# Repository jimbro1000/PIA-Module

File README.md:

# HD6309SBC PIA Prototype Module Board

This is an expansion board for the HD6309 
single board computer I designed (see 
https://github.com/jimbro1000/HD6309sbc).

The board uses the highly adaptable
MC6821 as the basis of the design but it
is advised to use the WDC65C21N as a 
substitute to guarantee handling of the
3MHz clock speed used by default.

Dropping the clock speed on the main
compute board will allow the use of
lower rated PIAs

By default the MC6821 is rated at only
1MHz.  
The A rated chip (68A21) is safe to 1.5MHz.  
The B rated chip (68B21) is safe to 2MHz.

Compatible variants are similarly rated
and also top out at 2MHz.

The board includes an 8x32 prototype area
while PL1 exposes all 16 data lanes
available to the PIA. PL2 exposes the
4 PIA control lines (CA0,CA1,CB0,CB1) and
various useful signals from the main
board along with +5V and GND.

The available signal lines are CPU clock
and switched control bits Q1-Q7

## Addressing

By default the PIA is addressable at $xx00 
through to $xx03. Optionally the addressing
can be modified to sit at $xx04 (to $xx07).

The value of xx is determined and managed by
the "mapped memory" signal line, this is
expected to be set to $FF00, so the default
PIA address is $FF00.

Each PIA block offers four registers:

* $FF00 = PIA Data Register A (PA0-PA7) or
Data Direction Register A
* $FF01 = PIA Control Register A
* $FF02 = PIA Data Register B (PB0-PB7) or
Data Direction Register B
* $FF03 = PIA Control Register B

## Example Usage - Keyboard Input

The PIA can be programmed to scan an 8x8
keyboard matrix, using PA0-PA7 for the
vertical and PB0-PB7 for the horizontal

The scan needs to be triggered on a timed
basis to scan and expose the captured data
on the main data bus

The control registers for both sides of
the PIA need to be set for input and this
needs a sequence of writes:

1. bit 2 of control register A must be
set low
2. input bits of data register A must
be set low
3. bit 2 of control register A must be
set high
4. bit 2 of control register B must be
set low
5. output bits of data register B must
be set high
6. bit 2 of control register B must be
set high

This leaves the relevant bits of data
registers A and B in input mode and 
the data registers exposed to the
address bus. Not all of the bits need
to be used and this will be determined
by the keyboard matrix. For example
the CoCo and Dragon keyboard matrices
use a 7x8 matrix (this *is* a 6809 based
computer).

In effect the single bits of register B
are set high in sequence, and at each
step register A is scanned to see which
keys are pressed for the given row or
column (depending on which way the 
matrix is oriented)

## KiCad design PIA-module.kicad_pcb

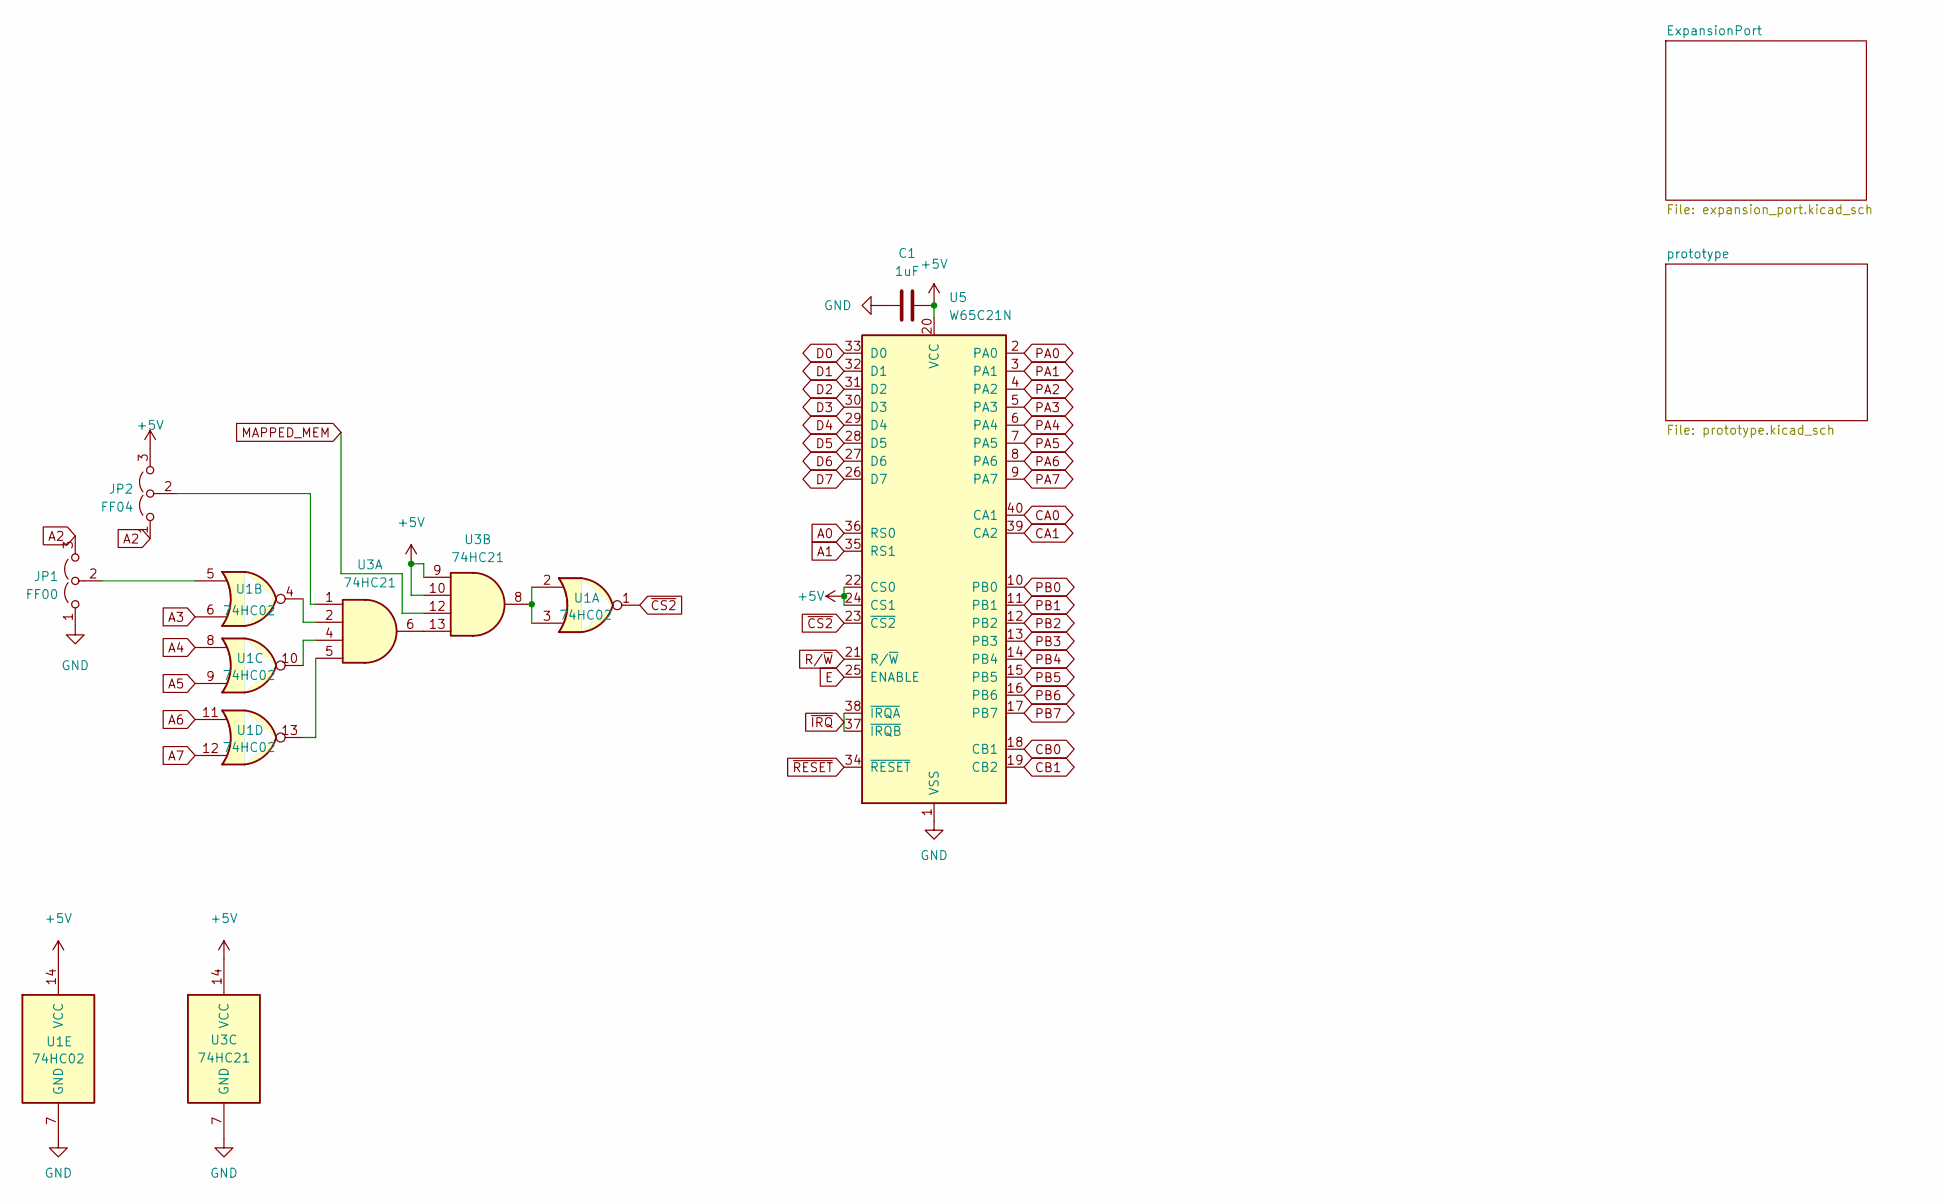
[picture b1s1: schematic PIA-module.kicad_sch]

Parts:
C1: 1uF; C_0805_2012Metric
JP1: FF00; PinHeader_1x03_P2.54mm_Vertical
JP2: FF04; PinHeader_1x03_P2.54mm_Vertical
U1: 74HC02; SO-14_3.9x8.65mm_P1.27mm
U3: 74HC21; SO-14_3.9x8.65mm_P1.27mm
U5: W65C21N; DIP-40_W15.24mm

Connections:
+5V: C1.1, JP2.3 (B), U1.14 (VCC), U3.9, U3.10, U3.14 (VCC), U5.20 (VCC), U5.22 (CS0), U5.24 (CS1); also elsewhere on the board
A0: U5.36 (RS0); also elsewhere on the board
A1: U5.35 (RS1); also elsewhere on the board
A2: JP1.3 (B), JP2.1 (A); also elsewhere on the board
A3: U1.6; also elsewhere on the board
A4: U1.8; also elsewhere on the board
A5: U1.9; also elsewhere on the board
A6: U1.11; also elsewhere on the board
A7: U1.12; also elsewhere on the board
CA0: U5.40 (CA1); also elsewhere on the board
CA1: U5.39 (CA2); also elsewhere on the board
CB0: U5.18 (CB1); also elsewhere on the board
CB1: U5.19 (CB2); also elsewhere on the board
D0: U5.33 (D0); also elsewhere on the board
D1: U5.32 (D1); also elsewhere on the board
D2: U5.31 (D2); also elsewhere on the board
D3: U5.30 (D3); also elsewhere on the board
D4: U5.29 (D4); also elsewhere on the board
D5: U5.28 (D5); also elsewhere on the board
D6: U5.27 (D6); also elsewhere on the board
D7: U5.26 (D7); also elsewhere on the board
E: U5.25 (ENABLE); also elsewhere on the board
GND: C1.2, JP1.1 (A), U1.7 (GND), U3.7 (GND), U5.1 (VSS); also elsewhere on the board
MAPPED_MEM: U3.12; also elsewhere on the board
unnamed: JP1.2 (C), U1.5
unnamed: JP2.2 (C), U3.1
unnamed: U1.2, U1.3, U3.8
unnamed: U1.4, U3.2
unnamed: U1.10, U3.4
unnamed: U1.13, U3.5
unnamed: U3.6, U3.13
PA0: U5.2 (PA0); also elsewhere on the board
PA1: U5.3 (PA1); also elsewhere on the board
PA2: U5.4 (PA2); also elsewhere on the board
PA3: U5.5 (PA3); also elsewhere on the board
PA4: U5.6 (PA4); also elsewhere on the board
PA5: U5.7 (PA5); also elsewhere on the board
PA6: U5.8 (PA6); also elsewhere on the board
PA7: U5.9 (PA7); also elsewhere on the board
PB0: U5.10 (PB0); also elsewhere on the board
PB1: U5.11 (PB1); also elsewhere on the board
PB2: U5.12 (PB2); also elsewhere on the board
PB3: U5.13 (PB3); also elsewhere on the board
PB4: U5.14 (PB4); also elsewhere on the board
PB5: U5.15 (PB5); also elsewhere on the board
PB6: U5.16 (PB6); also elsewhere on the board
PB7: U5.17 (PB7); also elsewhere on the board
R/~W: U5.21 (R/~W); also elsewhere on the board
~CS2: U1.1, U5.23 (~CS2)
~IRQ: U5.37 (~IRQB), U5.38 (~IRQA); also elsewhere on the board
~RESET: U5.34 (~RESET); also elsewhere on the board

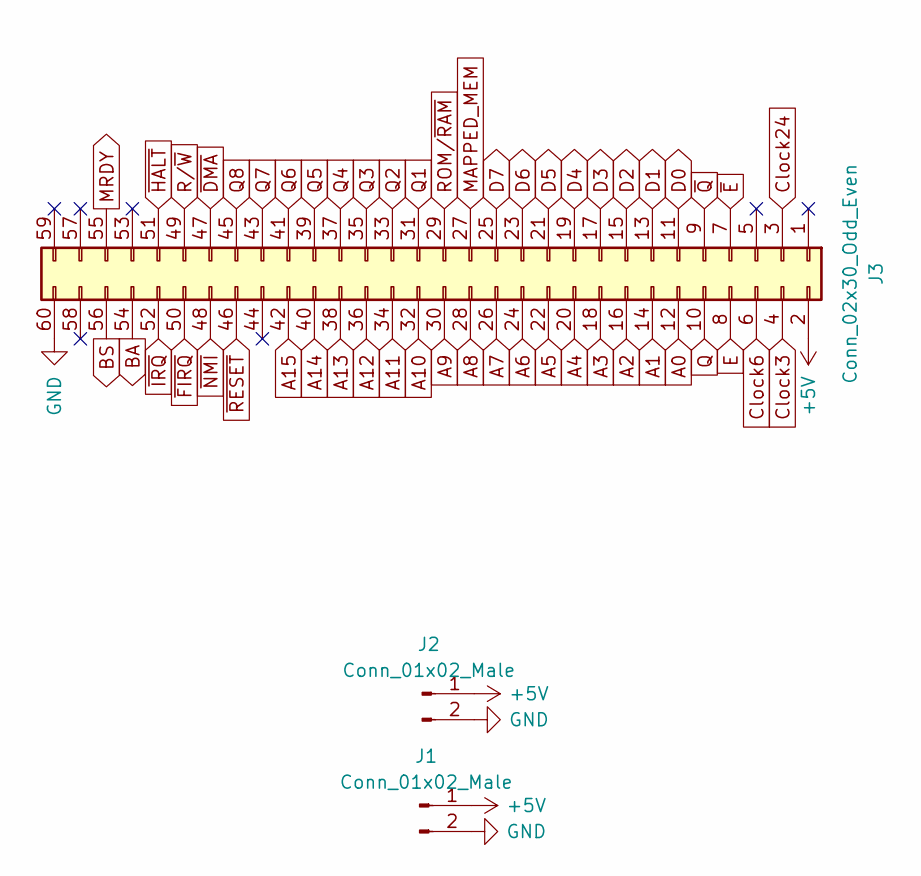
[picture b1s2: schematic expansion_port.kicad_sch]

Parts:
J1, J2: Conn_01x02_Male; PinHeader_1x02_P2.54mm_Vertical
J3: Conn_02x30_Odd_Even; PinHeader_2x30_P2.54mm_Vertical

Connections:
+5V: J1.1, J2.1, J3.2; also elsewhere on the board
A0: J3.12; also elsewhere on the board
A1: J3.14; also elsewhere on the board
A2: J3.16; also elsewhere on the board
A3: J3.18; also elsewhere on the board
A4: J3.20; also elsewhere on the board
A5: J3.22; also elsewhere on the board
A6: J3.24; also elsewhere on the board
A7: J3.26; also elsewhere on the board
A8: J3.28
A9: J3.30
A10: J3.32
A11: J3.34
A12: J3.36
A13: J3.38
A14: J3.40
A15: J3.42
BA: J3.54
BS: J3.56
Clock3: J3.4; also elsewhere on the board
Clock6: J3.6
Clock24: J3.3
D0: J3.11; also elsewhere on the board
D1: J3.13; also elsewhere on the board
D2: J3.15; also elsewhere on the board
D3: J3.17; also elsewhere on the board
D4: J3.19; also elsewhere on the board
D5: J3.21; also elsewhere on the board
D6: J3.23; also elsewhere on the board
D7: J3.25; also elsewhere on the board
E: J3.8; also elsewhere on the board
GND: J1.2, J2.2, J3.60; also elsewhere on the board
MAPPED_MEM: J3.27; also elsewhere on the board
MRDY: J3.55
Q: J3.10
Q1: J3.31; also elsewhere on the board
Q2: J3.33; also elsewhere on the board
Q3: J3.35; also elsewhere on the board
Q4: J3.37; also elsewhere on the board
Q5: J3.39; also elsewhere on the board
Q6: J3.41; also elsewhere on the board
Q7: J3.43; also elsewhere on the board
Q8: J3.45; also elsewhere on the board
ROM/~RAM: J3.29
R/~W: J3.49; also elsewhere on the board
~DMA: J3.47
~E: J3.7
~FIRQ: J3.50
~HALT: J3.51
~IRQ: J3.52; also elsewhere on the board
~NMI: J3.48
~Q: J3.9
~RESET: J3.46; also elsewhere on the board

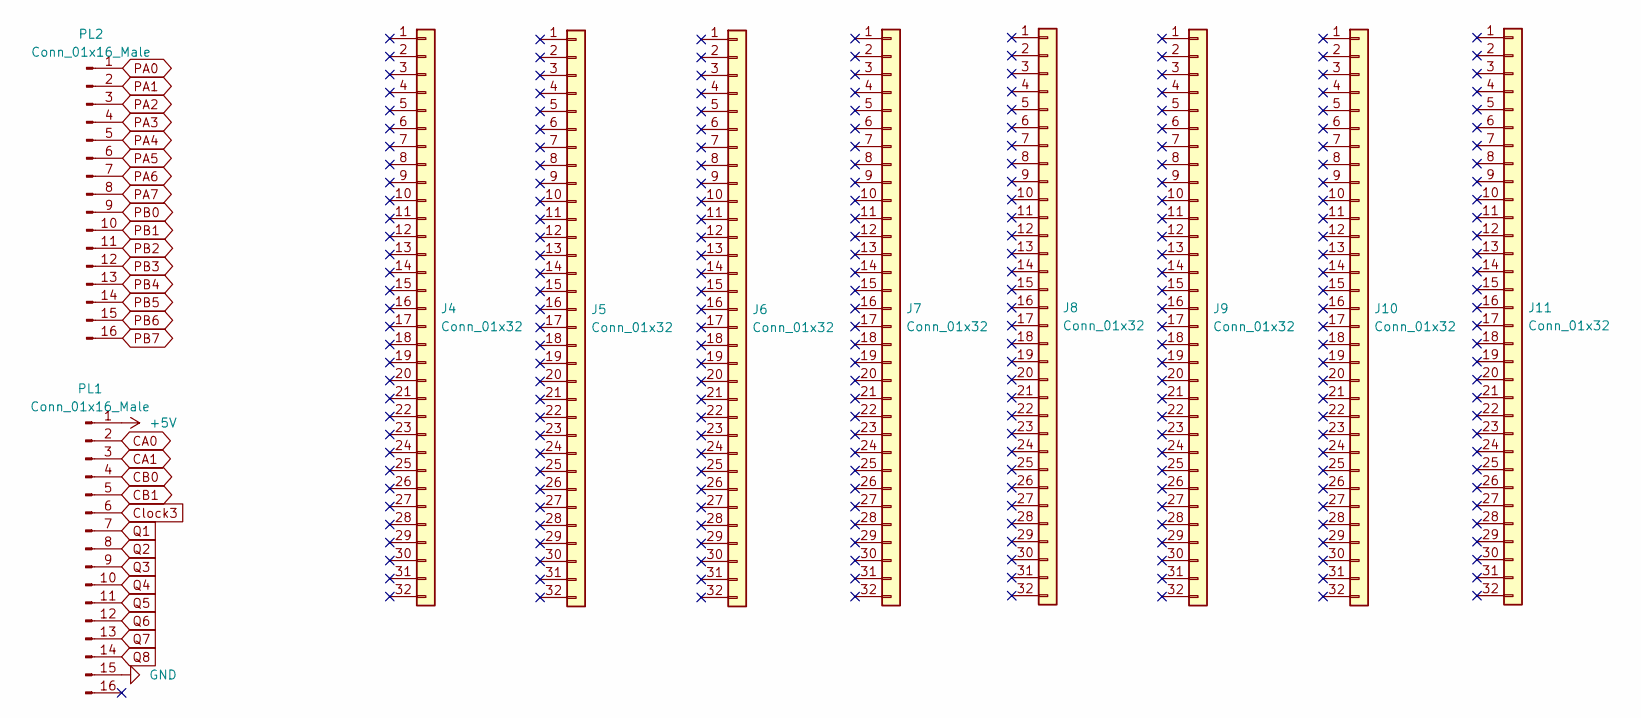
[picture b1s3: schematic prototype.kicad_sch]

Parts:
J4, J5, J6, J7, J8, J9, J10, J11: Conn_01x32; PinHeader_1x32_P2.54mm_Vertical
PL1, PL2: Conn_01x16_Male; PinHeader_1x16_P2.54mm_Vertical

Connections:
+5V: PL1.1; also elsewhere on the board
CA0: PL1.2; also elsewhere on the board
CA1: PL1.3; also elsewhere on the board
CB0: PL1.4; also elsewhere on the board
CB1: PL1.5; also elsewhere on the board
Clock3: PL1.6; also elsewhere on the board
GND: PL1.15; also elsewhere on the board
PA0: PL2.1; also elsewhere on the board
PA1: PL2.2; also elsewhere on the board
PA2: PL2.3; also elsewhere on the board
PA3: PL2.4; also elsewhere on the board
PA4: PL2.5; also elsewhere on the board
PA5: PL2.6; also elsewhere on the board
PA6: PL2.7; also elsewhere on the board
PA7: PL2.8; also elsewhere on the board
PB0: PL2.9; also elsewhere on the board
PB1: PL2.10; also elsewhere on the board
PB2: PL2.11; also elsewhere on the board
PB3: PL2.12; also elsewhere on the board
PB4: PL2.13; also elsewhere on the board
PB5: PL2.14; also elsewhere on the board
PB6: PL2.15; also elsewhere on the board
PB7: PL2.16; also elsewhere on the board
Q1: PL1.7; also elsewhere on the board
Q2: PL1.8; also elsewhere on the board
Q3: PL1.9; also elsewhere on the board
Q4: PL1.10; also elsewhere on the board
Q5: PL1.11; also elsewhere on the board
Q6: PL1.12; also elsewhere on the board
Q7: PL1.13; also elsewhere on the board
Q8: PL1.14; also elsewhere on the board

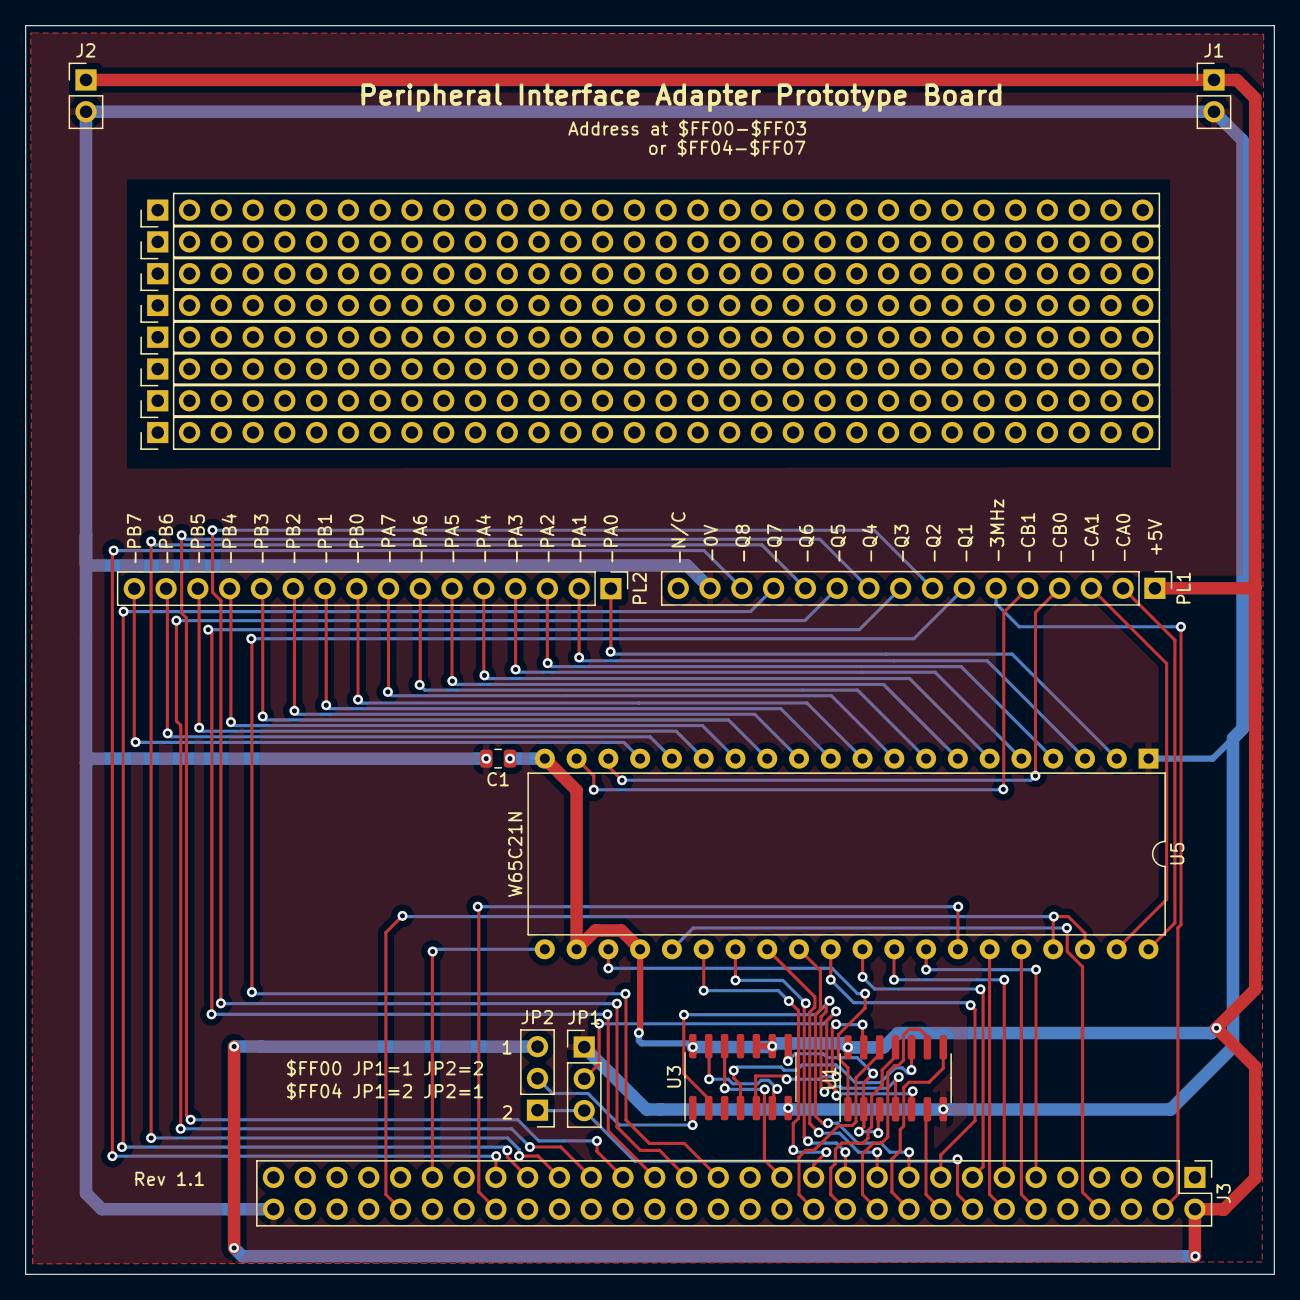
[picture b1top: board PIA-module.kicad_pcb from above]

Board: 2 copper layers, 99.8 x 99.8 mm, 19 parts (0 on the bottom side), 60 nets.

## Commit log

2022-10-08 add mapped memory lane
2023-04-10 add routing
2023-04-11 update README with addressing details
